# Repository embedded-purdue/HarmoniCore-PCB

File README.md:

# HarmoniCore-PCB
FPGA based Autotuner (PCB)

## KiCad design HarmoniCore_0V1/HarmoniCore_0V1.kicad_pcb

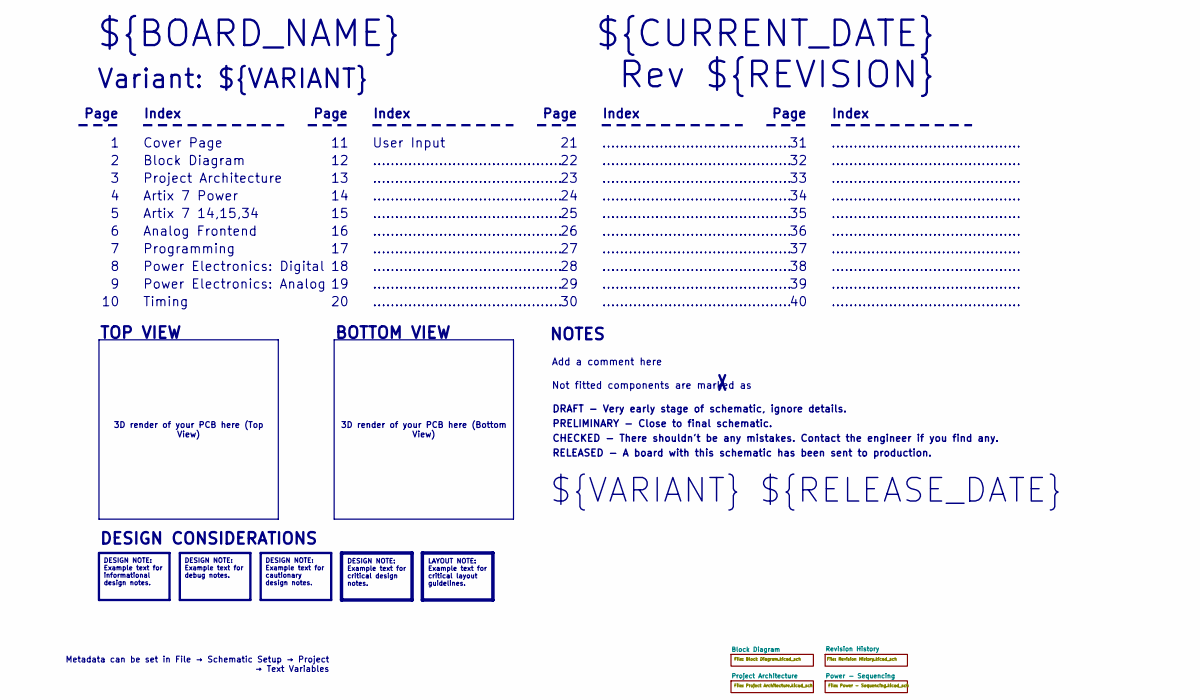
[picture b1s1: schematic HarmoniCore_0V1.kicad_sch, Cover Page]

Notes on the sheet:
BOTTOM VIEW
...........................................
RELEASED - A board with this schematic has been sent to production.
Page
TOP VIEW
Timing
Power Electronics: Analog
Power Electronics: Digital
Not fitted components are marked as
Index
PRELIMINARY - Close to final schematic.
${VARIANT} ${RELEASE_DATE}
Artix 7 Power
${CURRENT_DATE}
Variant: ${VARIANT}
Rev ${REVISION}
Artix 7 14,15,34
User Input
${BOARD_NAME}
DRAFT - Very early stage of schematic, ignore details.
Analog Frontend
Block Diagram
Add a comment here
Cover Page
NOTES
Project Architecture
CHECKED - There shouldn't be any mistakes. Contact the engineer if you find any.
DESIGN CONSIDERATIONS
Programming
3D render of your PCB here (Bottom View)
3D render of your PCB here (Top View)
Metadata can be set in File → Schematic Setup → Project → Text Variables
DESIGN NOTE: Example text for informational design notes.
LAYOUT NOTE: Example text for critical layout guidelines.
DESIGN NOTE: Example text for cautionary design notes.
DESIGN NOTE: Example text for debug notes.
DESIGN NOTE: Example text for critical design notes.

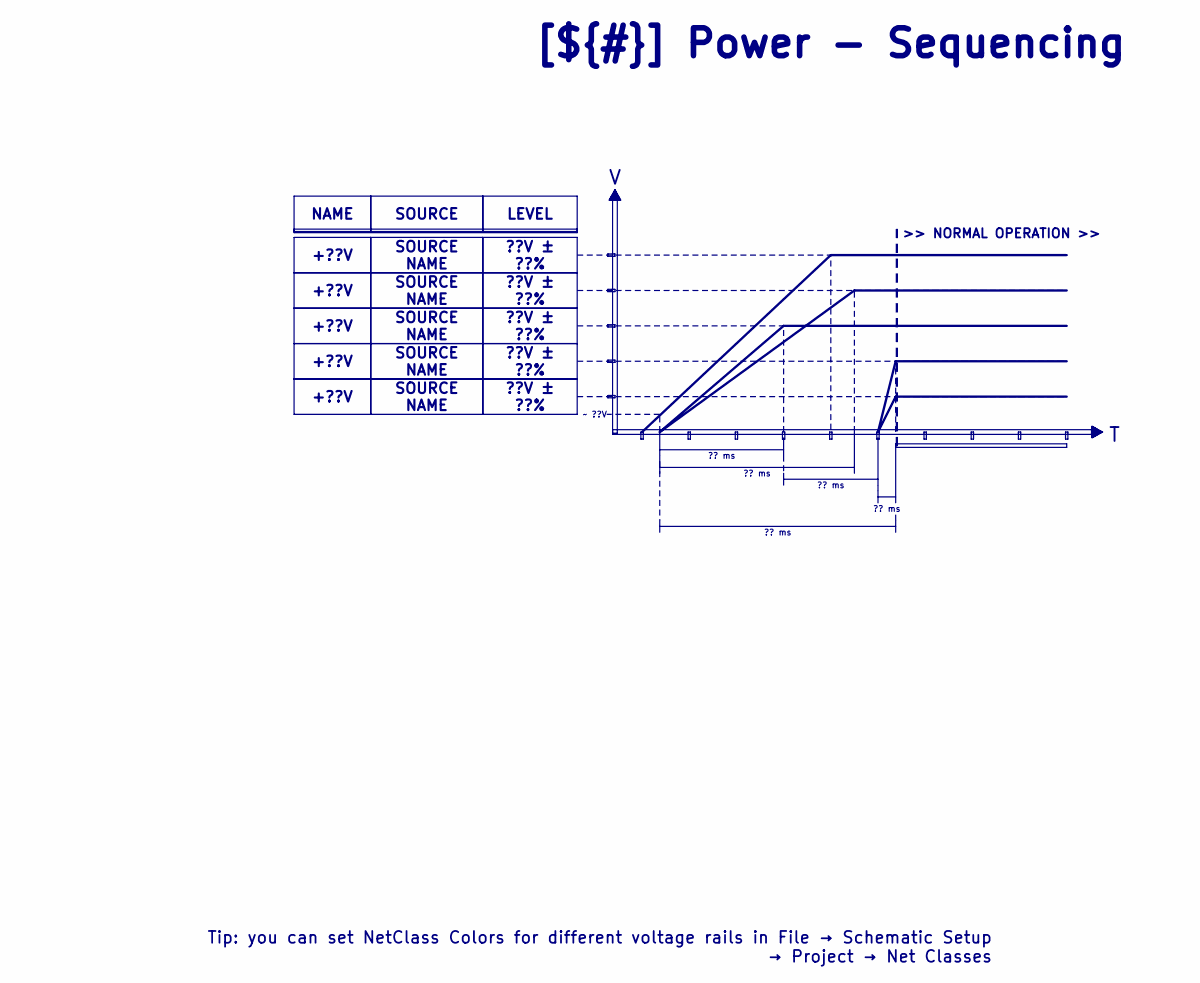
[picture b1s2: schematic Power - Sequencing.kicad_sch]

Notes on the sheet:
>> NORMAL OPERATION >>
LEVEL
+??V
SOURCE NAME
?? ms
??V ± ??%
[${#}] ${TITLE}
~ ??V
NAME
SOURCE
Tip: you can set NetClass Colors for different voltage rails in File → Schematic Setup → Project → Net Classes

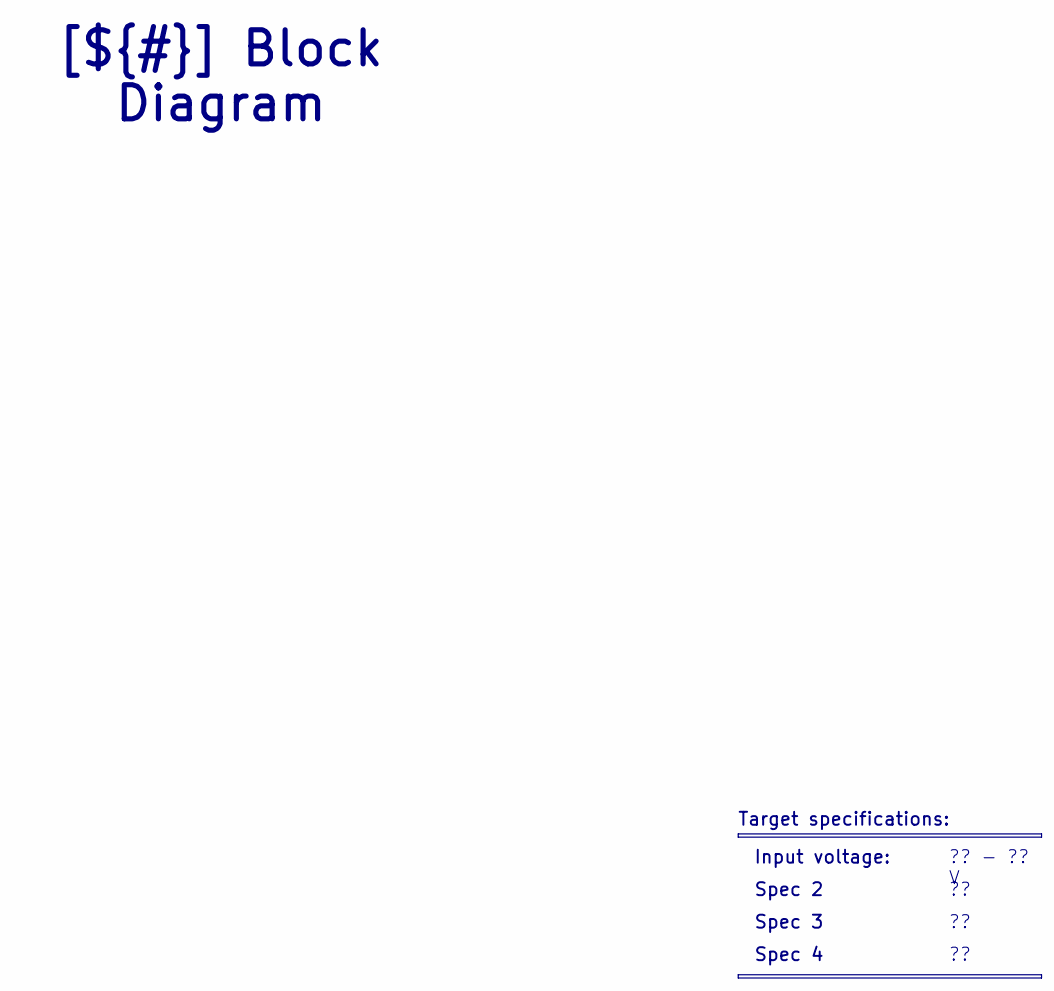
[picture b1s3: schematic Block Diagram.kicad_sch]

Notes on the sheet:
Spec 3
Spec 2
Input voltage:
[${#}] ${TITLE}
Target specifications:
?? - ?? V
Spec 4

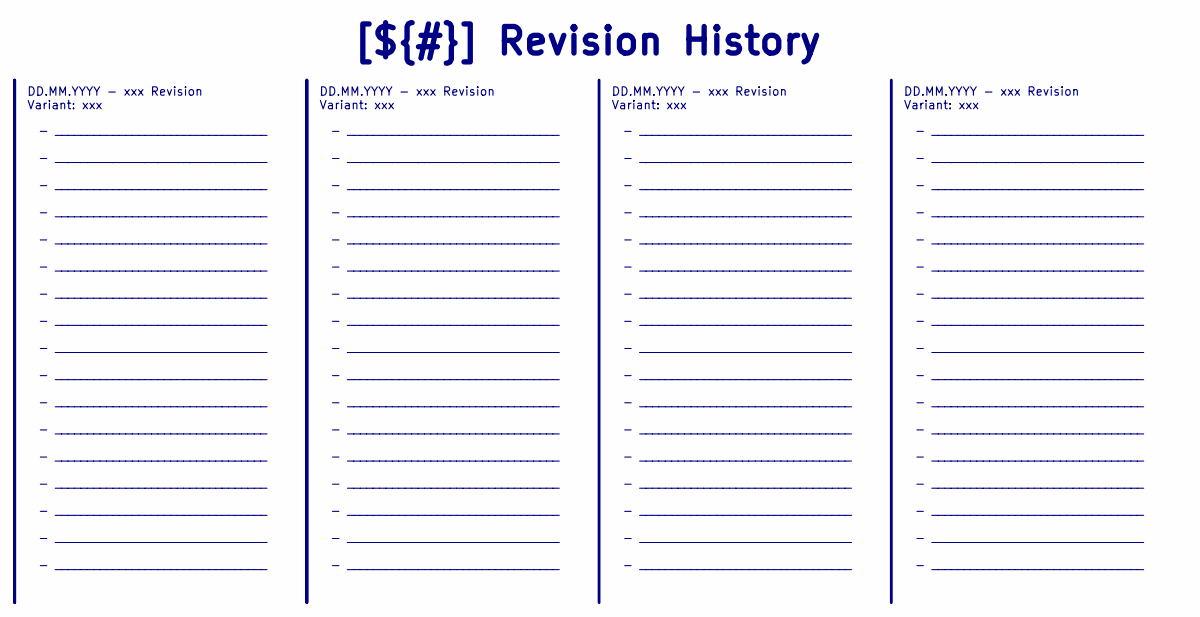
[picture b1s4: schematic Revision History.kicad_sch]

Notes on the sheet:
- _________________________________ - _________________________________ - _________________________________ - _________________________________ - _________________________________ - _________________________________ - _________________________________ - _________________________________ - _________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
DD.MM.YYYY - xxx Revision Variant: xxx
[${#}] ${TITLE}

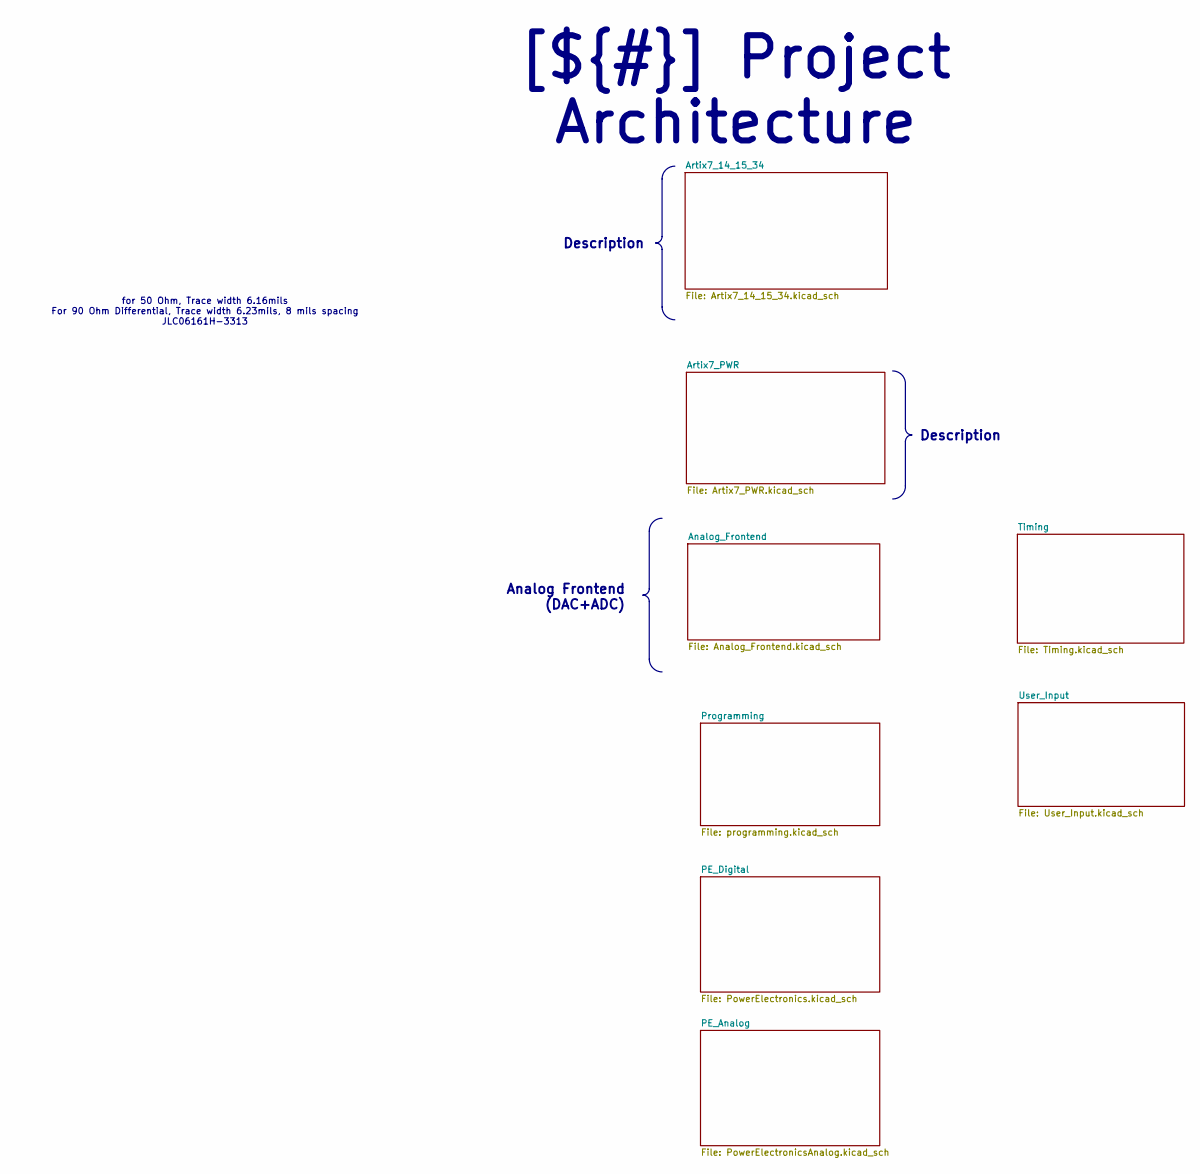
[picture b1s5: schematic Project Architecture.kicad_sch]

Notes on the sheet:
for 50 Ohm, Trace width 6.16mils For 90 Ohm Differential, Trace width 6.23mils, 8 mils spacing JLC06161H-3313
Analog Frontend (DAC+ADC)
Description
[${#}] ${TITLE}

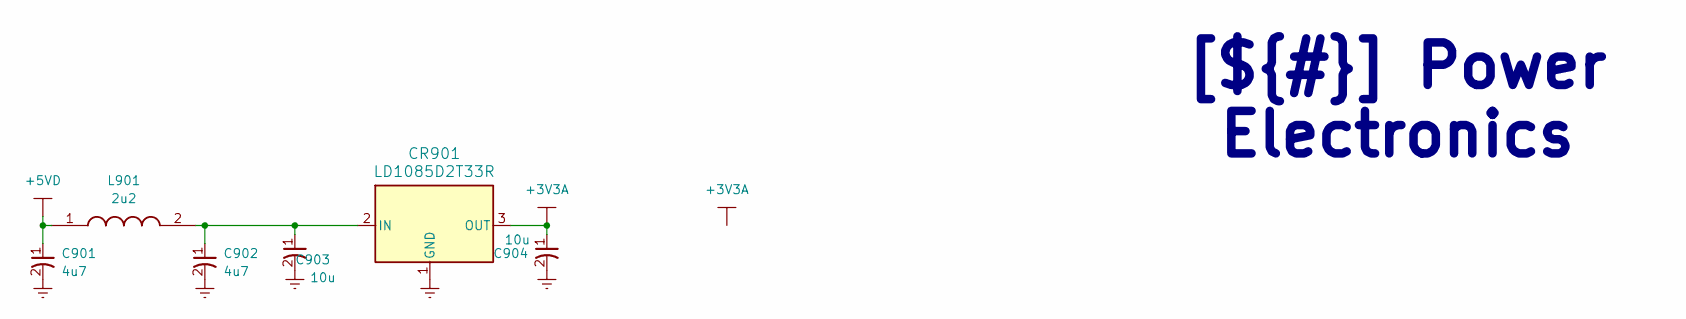
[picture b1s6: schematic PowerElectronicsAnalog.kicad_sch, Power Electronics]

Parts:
C901: 4u7; C_0805; Part Number GRM21BR71A475KA73K; DigiKey Part Number 490-6479-2-ND
C902: 4u7; TAJA475K016RNJ; PARTREV 031320
C903, C904: 10u; TAJA475K016RNJ; PARTREV 031320
CR901: LD1085D2T33R; Part Number LD1085D2T33R
L901: 2u2; INDC2520X120N; Mouser Part Number 652-SRP2512A-2R2M

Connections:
+3V3A: C904.1, CR901.3 (OUT); also elsewhere on the board
+5VA: C901.1, L901.1; also elsewhere on the board
Earth: C901.2, C902.2, C903.2, C904.2, CR901.1 (GND); also elsewhere on the board
unnamed: C902.1, C903.1, CR901.2 (IN), L901.2

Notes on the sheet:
[${#}] ${TITLE}

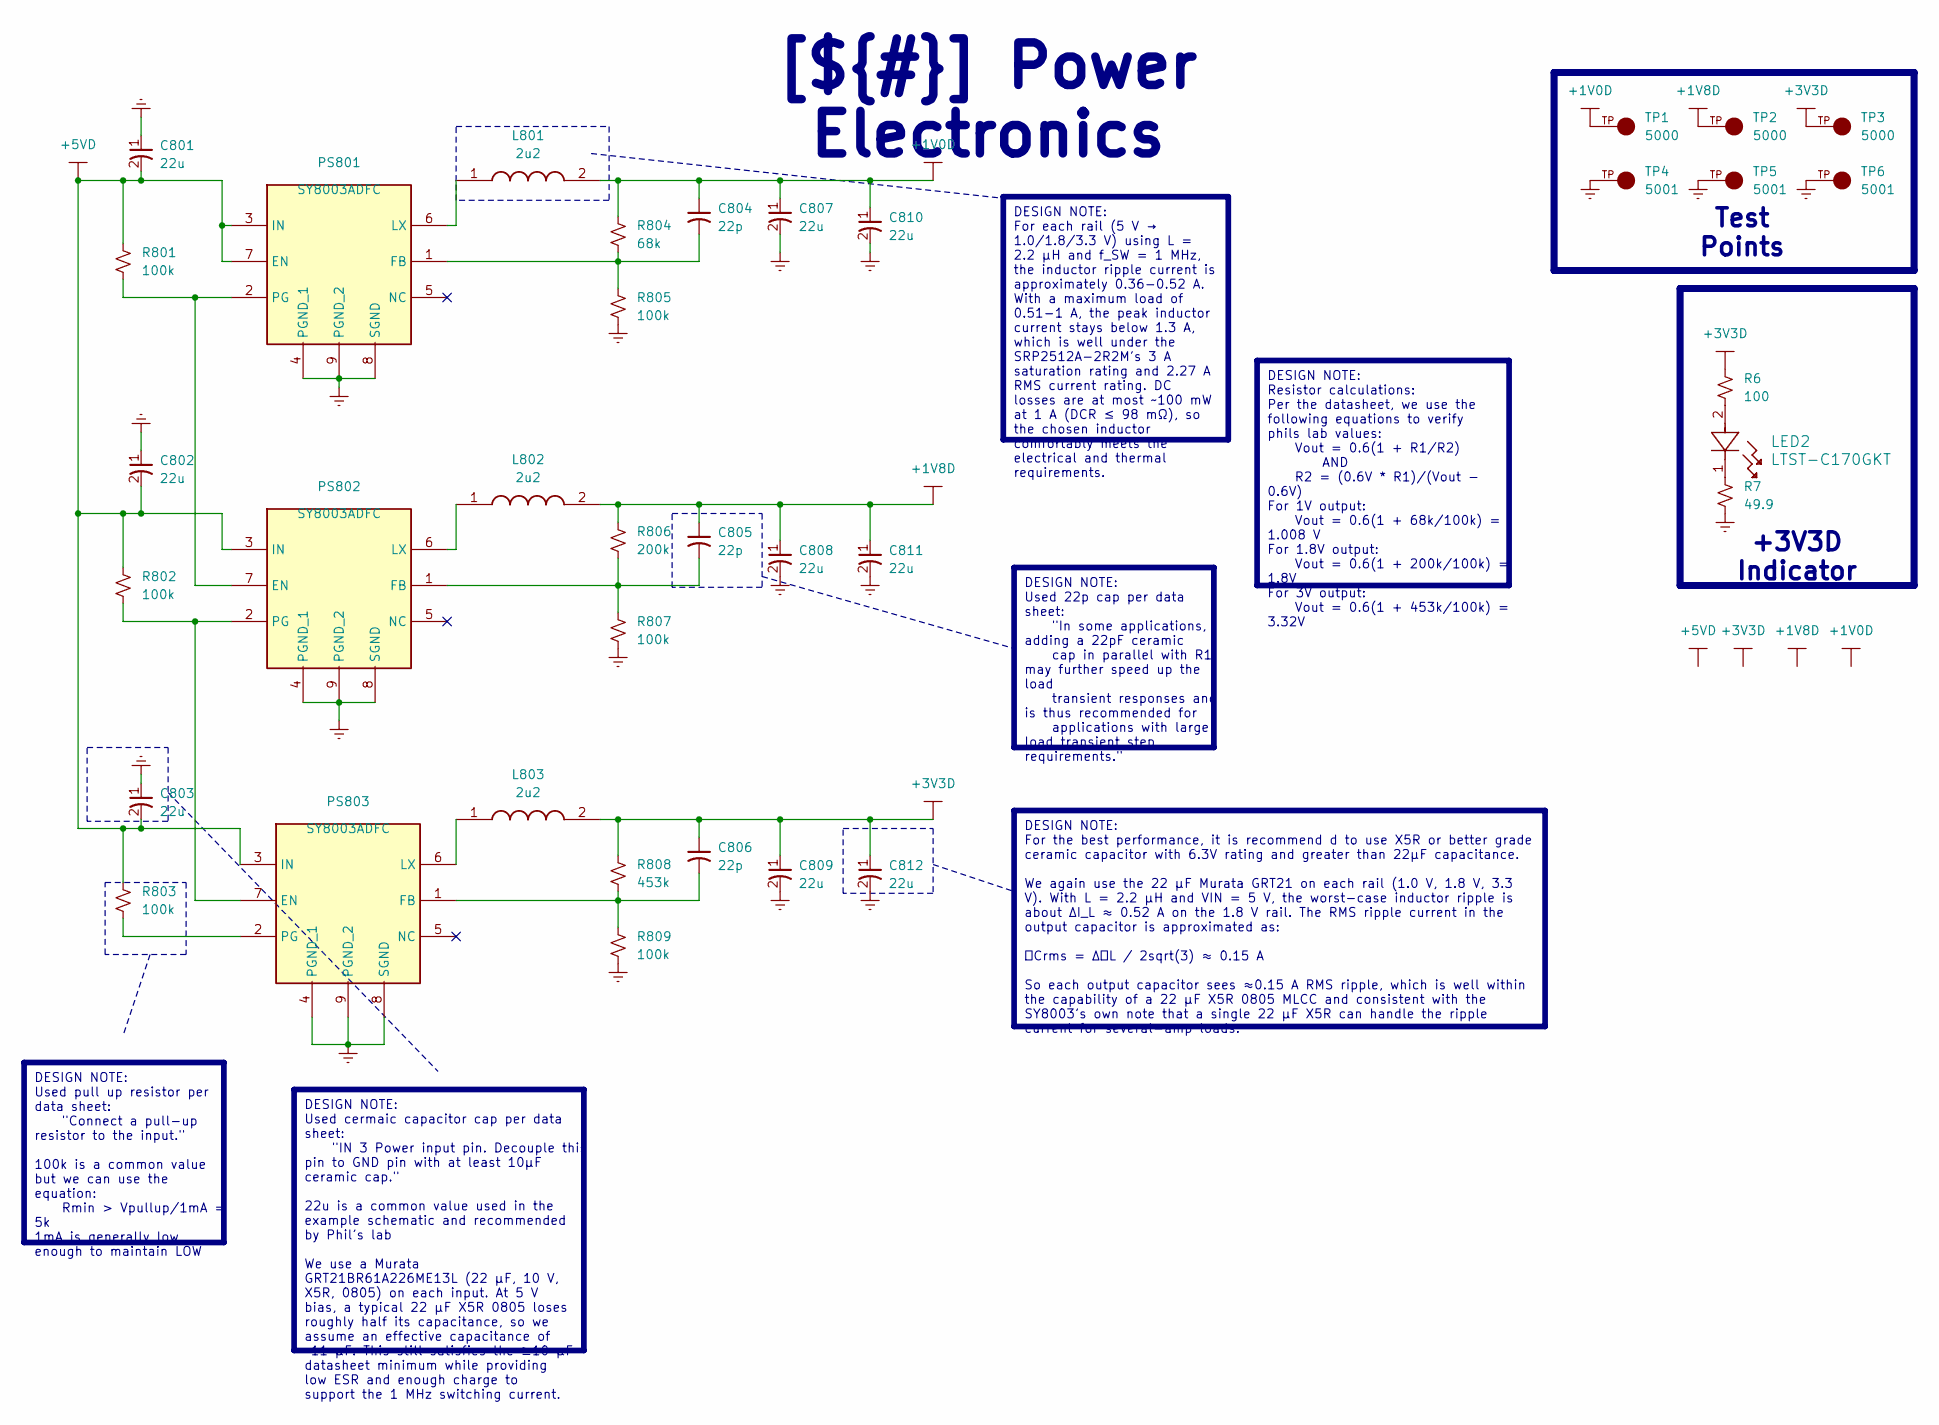
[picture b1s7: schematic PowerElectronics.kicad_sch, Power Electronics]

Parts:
C801, C802, C803, C807, C808, C809, C810, C811, C812: 22u; C_0805; Part Number GRT21BR61A226ME13L; DigiKey Part Number 490-12374-2-ND - Tape & Reel (TR) 490-1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
C804, C805, C806: 22p; C_0402
L801, L802, L803: 2u2; INDC2520X120N; Mouser Part Number 652-SRP2512A-2R2M
LED2: LTST-C170GKT; LED_0805
PS801, PS802, PS803: SY8003ADFC; Manufacturer_Part_Number SY8003ADFC; LCSC Part Number C178236
R6: 100; R_0603
R7: 49.9; R_0603
R801, R802, R803, R805, R807, R809: 100k; R_0603
R804: 68k; R_0603
R806: 200k; R_0603
R808: 453k; R_0603
TP1, TP2, TP3: 5000; KEYSTONE_5001; PARTREV H
TP4, TP5, TP6: 5001; KEYSTONE_5001; PARTREV H

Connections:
+1V0D: C804.1, C807.1, C810.1, L801.2, R804.2, TP1.TP; also elsewhere on the board
+1V8D: C805.1, C808.1, C811.1, L802.2, R806.2, TP2.TP; also elsewhere on the board
+3V3D: C806.1, C809.1, C812.1, L803.2, R6.2, R808.2, TP3.TP; also elsewhere on the board
+5VA: C801.2, C802.2, C803.2, PS801.3 (IN), PS801.7 (EN), PS802.3 (IN), PS803.3 (IN), R801.1, R802.1, R803.1; also elsewhere on the board
Earth: C801.1, C802.1, C803.1, C807.2, C808.2, C809.2, C810.2, C811.2, C812.2, PS801.4 (PGND_1), PS801.8 (SGND), PS801.9 (PGND_2), PS802.4 (PGND_1), PS802.8 (SGND), PS802.9 (PGND_2), PS803.4 (PGND_1), PS803.8 (SGND), PS803.9 (PGND_2), R7.1, R805.1, R807.2, R809.2, TP4.TP, TP5.TP, TP6.TP; also elsewhere on the board
unnamed: LED2.1, R7.2
unnamed: LED2.2, R6.1
unnamed: C804.2, PS801.1 (FB), R804.1, R805.2
unnamed: L801.1, PS801.6 (LX)
unnamed: PS801.2 (PG), PS802.7 (EN), R801.2
unnamed: C805.2, PS802.1 (FB), R806.1, R807.1
unnamed: L802.1, PS802.6 (LX)
unnamed: PS802.2 (PG), PS803.7 (EN), R802.2
unnamed: C806.2, PS803.1 (FB), R808.1, R809.1
unnamed: L803.1, PS803.6 (LX)
unnamed: PS803.2 (PG), R803.2

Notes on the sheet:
DESIGN NOTE: Resistor calculations: Per the datasheet, we use the following equations to verify phils lab values: Vout = 0.6(1 + R1/R2) AND R2 = (0.6V * R1)/(Vout - 0.6V) For 1V output: Vout = 0.6(1 + 68k/100k) = 1.008 V For 1.8V output: Vout = 0.6(1 + 200k/100k) = 1.8V For 3V output: Vout = 0.6(1 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
[${#}] ${TITLE}
DESIGN NOTE: Used 22p cap per data sheet: "In some applications, adding a 22pF ceramic cap in parallel with R1 may further speed up the load transient responses and is thus recommended for applications with large load transient step requirements."
DESIGN NOTE: Used pull up resistor per data sheet: "Connect a pull-up resistor to the input." 100k is a common value but we can use the equation: Rmin > Vpullup/1mA = 5k 1mA is generally low enough to maintain LOW
DESIGN NOTE: For each rail (5 V → 1.0/1.8/3.3 V) using L = 2.2 µH and f_SW = 1 MHz, the inductor ripple current is approximately 0.36-0.52 A. With a maximum load of 0.51-1 A, the peak inductor current stays below 1.3 A, which is well under the SRP2512A-2R2M's 3 A saturation rating and 2.27 A RMS cu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
DESIGN NOTE: Used cermaic capacitor cap per data sheet: "IN 3 Power input pin. Decouple this pin to GND pin with at least 10µF ceramic cap." 22u is a common value used in the example schematic and recommended by Phil's lab We use a Murata GRT21BR61A226ME13L (22 µF, 10 V, X5R, 0805) on each input. A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
+3V3D Indicator
DESIGN NOTE: For the best performance, it is recommend d to use X5R or better grade ceramic capacitor with 6.3V rating and greater than 22µF capacitance. We again use the 22 µF Murata GRT21 on each rail (1.0 V, 1.8 V, 3.3 V). With L = 2.2 µH and VIN = 5 V, the worst-case inductor ripple is about ΔI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
Test Points

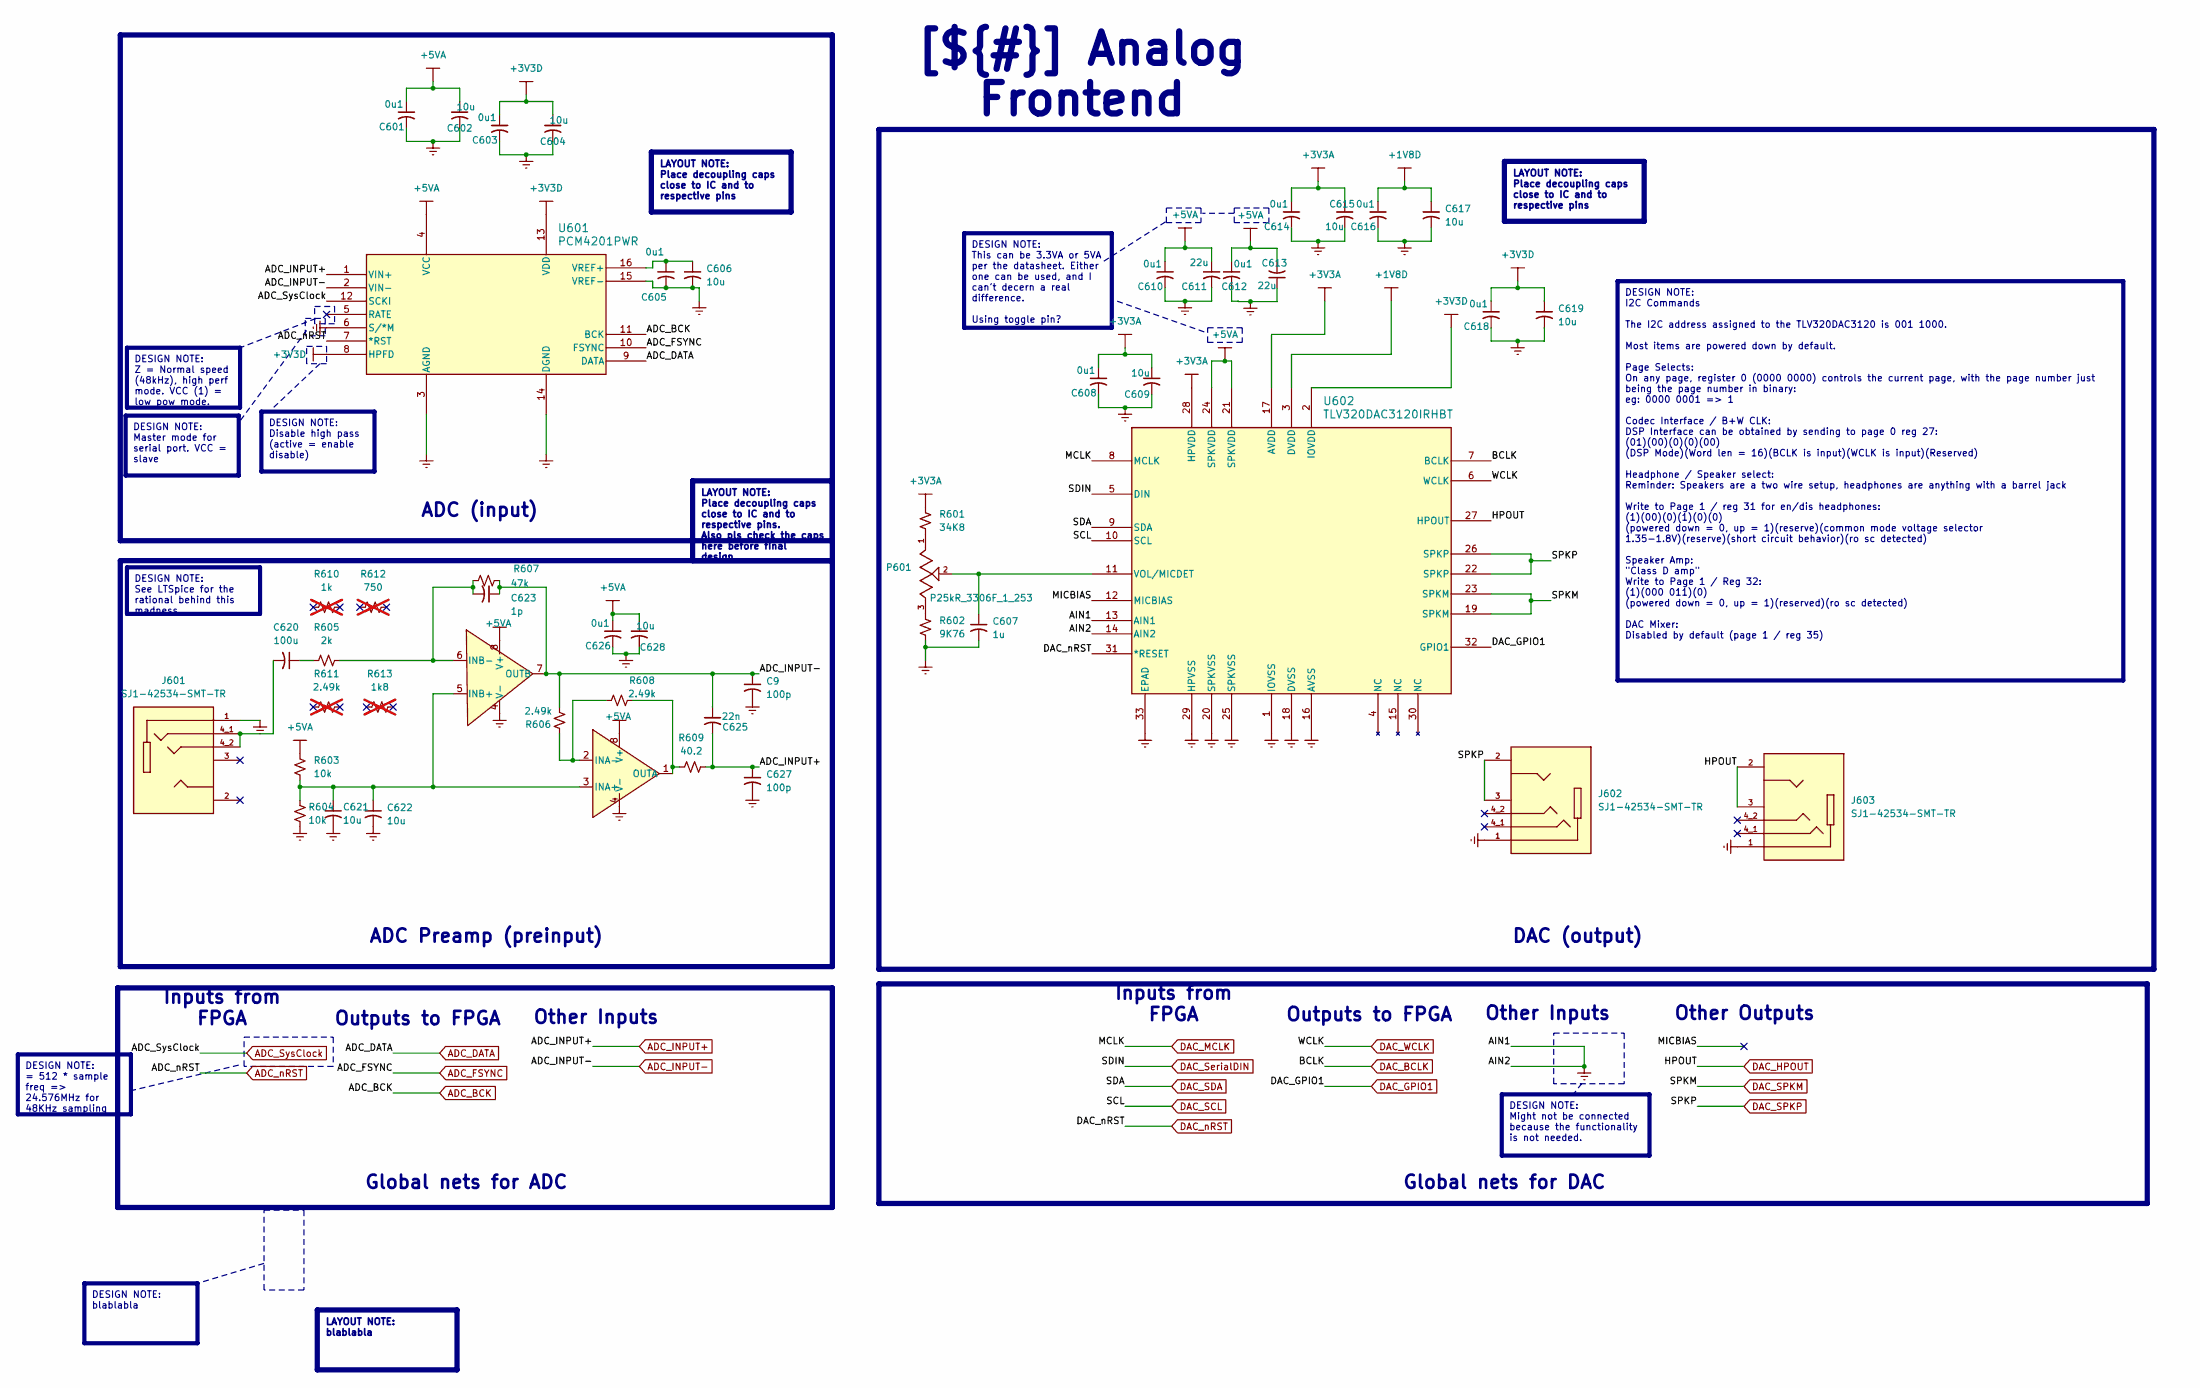
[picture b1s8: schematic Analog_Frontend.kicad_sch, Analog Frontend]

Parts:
C9, C627: 100p; C_0603
C601, C603, C605, C608, C610, C612, C614, C616, C618, C626: 0u1; C_0603
C602, C604, C606, C609, C615, C617, C619, C621, C622, C628: 10u; C_0603
C607: 1u; C_0603
C611, C613: 22u; C_0603
C620: 100u; C_1210
C623: 1p; C_0603
C625: 22n; C_0603
J601, J602, J603: SJ1-42534-SMT-TR; CUI_SJ1-42534-SMT-TR; PART_REV 1.06
P601: P25kR_3306F_1_253; Pot25kR_THT3306F-1-253; PARTREV 08/19
R601: 34K8; R_0603
R602: 9K76; R_0603
R603, R604: 10k; R_0603
R605: 2k; R_0603
R606, R608: 2.49k; R_0603
R607: 47k; R_0603
R609: 40.2; R_0603
R610: 1k; R_0603; not fitted
R611: 2.49k; R_0603; not fitted
R612: 750; R_0603; not fitted
R613: 1k8; R_0603; not fitted
U601: PCM4201PWR; PCM4201
U602: TLV320DAC3120IRHBT; TI_tlv320dac3120_DAC
U603: OPA2134UA/2K5; OPA2134UA_2K5

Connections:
+1V8D: C616.1, C617.1, U602.3 (DVDD); also elsewhere on the board
+3V3A: C608.1, C609.1, C614.1, C615.1, R601.2, U602.17 (AVDD), U602.28 (HPVDD); also elsewhere on the board
+3V3D: C603.1, C604.1, C618.1, C619.1, U601.8 (HPFD), U601.13 (VDD), U602.2 (IOVDD); also elsewhere on the board
+5VA: C601.1, C602.1, C610.1, C611.1, C612.1, C613.2, C626.1, C628.1, R603.2, U601.4 (VCC), U602.21 (SPKVDD), U602.24 (SPKVDD), U603.8 (V+); also elsewhere on the board
/Project Architecture/Analog_Frontend/MICBIAS: U602.12 (MICBIAS)
ADC_BCK: U601.11 (BCK); also elsewhere on the board
ADC_DATA: U601.9 (DATA); also elsewhere on the board
ADC_FSYNC: U601.10 (FSYNC); also elsewhere on the board
ADC_INPUT+: C625.2, C627.1, R609.1, U601.1 (VIN+)
ADC_INPUT-: C9.1, C623.1, C625.1, R606.2, R607.2, U601.2 (VIN-), U603.7 (OUTB)
ADC_SysClock: U601.12 (SCKI); also elsewhere on the board
ADC_nRST: U601.7 (*RST); also elsewhere on the board
DAC_BCLK: U602.7 (BCLK); also elsewhere on the board
DAC_GPIO1: U602.32 (GPIO1); also elsewhere on the board
DAC_HPOUT: J603.2, J603.3, U602.27 (HPOUT)
DAC_MCLK: U602.8 (MCLK); also elsewhere on the board
DAC_SCL: U602.10 (SCL); also elsewhere on the board
DAC_SDA: U602.9 (SDA); also elsewhere on the board
DAC_SPKM: U602.19 (SPKM), U602.23 (SPKM)
DAC_SPKP: J602.2, J602.3, U602.22 (SPKP), U602.26 (SPKP)
DAC_SerialDIN: U602.5 (DIN); also elsewhere on the board
DAC_WCLK: U602.6 (WCLK); also elsewhere on the board
DAC_nRST: U602.31 (*RESET); also elsewhere on the board
Earth: C9.2, C601.2, C602.2, C603.2, C604.2, C605.2, C606.2, C607.2, C608.2, C609.2, C610.2, C611.2, C612.2, C613.1, C614.2, C615.2, C616.2, C617.2, C618.2, C619.2, C621.2, C622.2, C626.2, C627.2, C628.2, J601.1, J602.1, J603.1, R602.1, R604.1, U601.3 (AGND), U601.6 (S/*M), U601.14 (DGND), U601.15 (VREF-), U602.1 (IOVSS), U602.13 (AIN1), U602.14 (AIN2), U602.16 (AVSS), U602.18 (DVSS), U602.20 (SPKVSS), U602.25 (SPKVSS), U602.29 (HPVSS), U602.33 (EPAD), U603.4 (V-); also elsewhere on the board
unnamed: C620.1, R605.1
unnamed: C620.2, J601.4_1, J601.4_2
unnamed: P601.1, R601.1
unnamed: P601.3, R602.2
unnamed: C605.1, C606.1, U601.16 (VREF+)
unnamed: C607.1, P601.2, U602.11 (VOL/MICDET)
unnamed: C621.1, C622.1, R603.1, R604.2, U603.3 (INA+), U603.5 (INB+)
unnamed: R606.1, R608.2, U603.2 (INA-)
unnamed: R608.1, R609.2, U603.1 (OUTA)
unnamed: C623.2, R605.2, R607.1, U603.6 (INB-)

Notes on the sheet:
DESIGN NOTE: blablabla
DESIGN NOTE: Z = Normal speed (48kHz), high perf mode. VCC (1) = low pow mode.
DESIGN NOTE: I2C Commands The I2C address assigned to the TLV320DAC3120 is 001 1000. Most items are powered down by default. Page Selects: On any page, register 0 (0000 0000) controls the current page, with the page number just being the page number in binary: eg: 0000 0001 => 1 Codec Interface / B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
ADC (input)
DESIGN NOTE: = 512 * sample freq => 24.576MHz for 48KHz sampling
Other Inputs
Global nets for ADC
LAYOUT NOTE: Place decoupling caps close to IC and to respective pins
DESIGN NOTE: Might not be connected because the functionality is not needed.
LAYOUT NOTE: blablabla
[${#}] ${TITLE}
Global nets for DAC
DESIGN NOTE: Master mode for serial port. VCC = slave
DESIGN NOTE: This can be 3.3VA or 5VA per the datasheet. Either one can be used, and I can't decern a real difference. Using toggle pin?
LAYOUT NOTE: Place decoupling caps close to IC and to respective pins. Also pls check the caps here before final design.
DESIGN NOTE: See LTSpice for the rational behind this madness
Inputs from FPGA
DESIGN NOTE: Disable high pass (active = enable disable)
ADC Preamp (preinput)
Other Outputs
Outputs to FPGA
DAC (output)

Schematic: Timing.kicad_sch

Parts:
C1001, C1002: 10u; C_0603
R1001, R1003: 33; R_0603
R1002: 10k; R_0603
Y1001: ECS-2520MV-120-BN-TR; PARTREV 2022
Y1002: SiT8209AI-82-18S-155.520000; QFN_7050_4pins

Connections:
12M_FTDI: R1001.2; also elsewhere on the board
156M_A7: R1003.2; also elsewhere on the board
+3V3D: C1001.1, C1002.1, R1002.2, Y1001.4 (VDD), Y1002.4 (VDD); also elsewhere on the board
Earth: C1001.2, C1002.2, Y1001.2 (GND), Y1002.2 (GND); also elsewhere on the board
unnamed: R1001.1, Y1001.3 (OUTPUT)
unnamed: R1002.1, Y1002.1 (OE/~ST)
unnamed: R1003.1, Y1002.3 (OUT)

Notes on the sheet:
[${#}] ${TITLE}
FTDI Oscillator
GLOBAL NETS
FPGA 156MHz Clock

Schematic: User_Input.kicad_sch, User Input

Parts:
C1101, C1105, C1106: 0u1; C_0603
C1102, C1103: 4u7; C_0603
C1104, C1107: 22u; C_0603
FB1101: FB600R_0603; BEADC1608X95N
H1101: Jumper
J1101: Conn_01x03; PinHeader_1x03_P2.54mm_Vertical
J1102: Conn_01x06; PinHeader_1x06_P2.54mm_Vertical
J1103: USB-C; GCT_USB4105-GF-A
J1104: DC_Jack; CONN3_54-00166_TEN
Q1101: AO3401A; SOT-23-3L_AOS-L
R1101, R1102, R1103, R1104, R1105, R1107, R1114, R1115, R1116, R1132: 10k; R_0603
R1106, R1117, R1118, R1119, R1120, R1121, R1122, R1123, R1124, R1125, R1126, R1127, R1128, R1129, R1130, R1131, R1134, R1135, R1136, R1137: 100k; R_0603
R1108, R1109, R1110, R1111: 22; R_0603
R1112, R1113: 5.1k; R_0603
R1133: 2k; R_0603
S1101, S1102, S1103, S1104: 219-3LPST; 2193LPST
SW1101, SW1102, SW1103: SW_Push; SMD_F260QG_EWI-L
U1101: LS1205EVD33; DFN10_3x3_LTF-L

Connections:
+3V3D: C1101.1, J1102.6, R1114.2, R1115.2, R1116.2, S1101.4, S1101.5, S1101.6, S1102.4, S1102.5, S1102.6, S1103.4, S1103.5, S1103.6, S1104.4, S1104.5, S1104.6; also elsewhere on the board
+5VA: C1107.1, U1101.8 (OUT), U1101.9 (OUT), U1101.10 (OUT); also elsewhere on the board
/Project Architecture/User_Input/HD_TCK: J1102.4, R1111.1
/Project Architecture/User_Input/HD_TDI: J1102.2, R1109.1
/Project Architecture/User_Input/HD_TDO: J1102.3, R1110.1
/Project Architecture/User_Input/HD_TMS: J1102.1, R1108.1
/Project Architecture/User_Input/PWR_SEL: J1101.2, Q1101.3 (D)
/Project Architecture/User_Input/PWR_USB: C1102.1, FB1101.1, J1103.VBUS
B1: R1114.1, SW1101.1; also elsewhere on the board
B2: R1115.1, SW1102.1; also elsewhere on the board
B3: R1116.1, SW1103.1; also elsewhere on the board
D_N: J1103.A7 (DN1), J1103.B7 (DN2); also elsewhere on the board
D_P: J1103.A6 (DP1), J1103.B6 (DP2); also elsewhere on the board
Earth: C1101.2, C1102.2, C1103.2, C1104.2, C1105.2, C1106.2, C1107.2, J1102.5, J1103.GND, J1103.SH (SHIELD), J1104.2, J1104.3, R1104.1, R1105.1, R1106.2, R1107.1, R1112.2, R1113.2, R1120.1, R1121.1, R1122.1, R1127.1, R1128.1, R1129.1, R1133.1, R1135.1, R1136.1, R1137.1, SW1101.2, SW1102.2, SW1103.2, U1101.11 (EPAD); also elsewhere on the board
M0: R1101.1; also elsewhere on the board
M1: R1102.1; also elsewhere on the board
M2: R1103.1; also elsewhere on the board
unnamed: J1103.A5 (CC1), R1112.1
unnamed: J1103.B5 (CC2), R1113.1
unnamed: Q1101.1 (G), R1106.1
unnamed: R1101.2, R1104.2, S1101.1
unnamed: R1102.2, R1105.2, S1101.2
unnamed: R1103.2, R1107.2, S1101.3
unnamed: R1117.2, R1120.2, S1102.1
unnamed: R1118.2, R1121.2, S1102.2
unnamed: R1119.2, R1122.2, S1102.3
unnamed: R1123.2, R1127.2, S1103.1
unnamed: R1125.2, R1128.2, S1103.2
unnamed: R1126.2, R1129.2, S1103.3
unnamed: R1130.2, R1135.2, S1104.1
unnamed: R1131.2, R1136.2, S1104.2
unnamed: R1134.2, R1137.2, S1104.3
unnamed: C1105.1, R1124.1, U1101.7 (EN)
unnamed: R1133.2, U1101.5 (ILIM)
unnamed: C1106.1, U1101.6 (SS)
unnamed: R1132.1, U1101.4 (VCP)
S1: R1117.1; also elsewhere on the board
S2: R1118.1; also elsewhere on the board
S3: R1119.1; also elsewhere on the board
S4: R1123.1; also elsewhere on the board
S5: R1125.1; also elsewhere on the board
S6: R1126.1; also elsewhere on the board
S7: R1130.1; also elsewhere on the board
S8: R1131.1; also elsewhere on the board
S9: R1134.1; also elsewhere on the board
TCK: R1111.2; also elsewhere on the board
TDI: R1109.2; also elsewhere on the board
TDO: R1110.2; also elsewhere on the board
TMS: R1108.2; also elsewhere on the board
VBUS: C1103.1, FB1101.2, J1101.3; also elsewhere on the board
VIN: C1104.1, Q1101.2 (S), R1124.2, R1132.2, U1101.1 (IN), U1101.2 (IN), U1101.3 (IN)
VJACK: J1101.1, J1104.1

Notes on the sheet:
[${#}] ${TITLE}
MISC BUTTONS
DESIGN NOTE: VCP = 1 -> 5V Operation Ilim = 10.5 / 2 = 5.25A
GLOBAL NETS
BOOT
DC-Jack
M[2:0] = 101 JTAG M[2:0] = 001 SPI
JTAG
Power Input Select
eFuse
USB-C

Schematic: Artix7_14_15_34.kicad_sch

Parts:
R501: 22; R_0603
R502: 49.9; R_0603
R503, R504, R505, R506: 4k7; R_0603
U401: XC7A25T-CSG325; Xilinx_CSG325

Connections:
156M_A7: U401.R1 (IO_L13N_T2_MRCC_34); also elsewhere on the board
+3V3D: R503.2, R504.2; also elsewhere on the board
ADC_BCK: U401.T18 (IO_L15N_T2_DQS_DOUT_CSO_B_14); also elsewhere on the board
ADC_DATA: U401.P18 (IO_L10N_T1_D15_14); also elsewhere on the board
ADC_FSYNC: U401.R18 (IO_L15P_T2_DQS_RDWR_B_14); also elsewhere on the board
ADC_SysClock: U401.P14 (IO_L12P_T1_MRCC_14); also elsewhere on the board
ADC_nRST: R506.2, U401.L18 (IO_L4N_T0_D05_14); also elsewhere on the board
B1: U401.A15 (IO_L10N_T1_AD4N_15); also elsewhere on the board
B2: U401.A17 (IO_L15N_T2_DQS_ADV_B_15); also elsewhere on the board
B3: U401.B16 (IO_L15P_T2_DQS_15); also elsewhere on the board
DAC_BCLK: U401.V16 (IO_L18P_T2_A12_D28_14); also elsewhere on the board
DAC_GPIO1: U401.V14 (IO_L20N_T3_A07_D23_14); also elsewhere on the board
DAC_MCLK: U401.T14 (IO_L13P_T2_MRCC_14); also elsewhere on the board
DAC_SCL: R503.1, U401.V12 (IO_L21P_T3_DQS_14); also elsewhere on the board
DAC_SDA: R504.1, U401.V13 (IO_L21N_T3_DQS_A06_D22_14); also elsewhere on the board
DAC_SerialDIN: U401.V17 (IO_L18N_T2_A11_D27_14); also elsewhere on the board
DAC_WCLK: U401.U17 (IO_L16N_T2_A15_D31_14); also elsewhere on the board
DAC_nRST: R505.2, U401.V11 (IO_L23N_T3_A02_D18_14); also elsewhere on the board
Earth: R501.1, R505.1, R506.1; also elsewhere on the board
unnamed: R502.2, U401.K18 (IO_L3N_T0_DQS_EMCCLK_14)
unnamed: R501.2, U401.J18 (IO_L3P_T0_DQS_PUDC_B_14)
QSPI_CLK: R502.1; also elsewhere on the board
QSPI_CS: U401.L15 (IO_L6P_T0_FCS_B_14); also elsewhere on the board
QSPI_DO0: U401.K16 (IO_L1P_T0_D00_MOSI_14); also elsewhere on the board
QSPI_DO1: U401.L17 (IO_L1N_T0_D01_DIN_14); also elsewhere on the board
QSPI_DO2: U401.J15 (IO_L2P_T0_D02_14); also elsewhere on the board
QSPI_DO3: U401.J16 (IO_L2N_T0_D03_14); also elsewhere on the board
S1: U401.A12 (IO_L7N_T1_AD10N_15); also elsewhere on the board
S2: U401.A13 (IO_L8P_T1_AD3P_15); also elsewhere on the board
S3: U401.A14 (IO_L8N_T1_AD3N_15); also elsewhere on the board
S4: U401.A10 (IO_L5N_T0_AD2N_15); also elsewhere on the board
S5: U401.C11 (IO_L4P_T0_AD9P_15); also elsewhere on the board
S6: U401.B11 (IO_L4N_T0_AD9N_15); also elsewhere on the board
S7: U401.B9 (IO_L3P_T0_DQS_AD1P_15); also elsewhere on the board
S8: U401.A9 (IO_L3N_T0_DQS_AD1N_15); also elsewhere on the board
S9: U401.B10 (IO_L5P_T0_AD2P_15); also elsewhere on the board

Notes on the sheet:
LAYOUT NOTE: Pending check IOs for general purpose
